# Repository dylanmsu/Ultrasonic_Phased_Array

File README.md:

# Ultrasonic_Phased_Array
This repository is under construction and will contain all the sources for a working ultrasonic phased array.
The vitis project in this repository is to be used in a accoustic levitation example.

## Working principle
Lets consider an example where we want to send a single pulse of airpressure to a certain point in space. We have an array of transducers we can work with. Since the waves travel in a sphere around the transducers, we can time the pulses at each transducer in such a way that all the wavefronts arrive at the same time in a single focal point. This is illustrated in the animation below.

If we were to send a sinewave with the same delay through the transducers instead of a single pulse, all the peaks and troughs of those waves would ideally only add up in the focal point. The amplitude would then be the greatest at that point and ideally cancel out everywhere else. This is actually not always the case because a side effect of using a periodic signal is that we create te posibility of sidelobes. Sidelobes are areas where some of the sinewaves constructively add up unwantedly where the phase shift is a multiple of 360 degrees. To prevent the occurance of sidelobes, we need to space the transducers with a distance between 1/2 wavelength, and 1/4 wavelength. 

To calculate the phase offsets per transducer for a single focal point, the following formula is used:
$$\varphi =  -\frac{2\pi\sqrt{(X_t - X_f)^2 + (Y_t - Y_f)^2 + (Z_t - Z_f)^2}}{\lambda}$$
Where: 
- $\varphi$ = the phase offset for a given transducer
- $X_t, Y_t, Z_t$ = the location of the transducer
- $X_f, Y_f, Z_f$ = the location of the focal point
- $\lambda$ = wavelength

The waves exiting the transducers will look something like this.

The red dots at the bottom are sources emitting pure sinusodial signals with an adjusted phase delay so all the waves are in phase at the red dot around the middle.

There is an included python script called 'wave_equation.py' that focuses the waves to your mouse location by manipulating the phases of the emitters. It solves the 2d wave equation so it should be more acurate than the above animation.

We can also steer a beam into a specified direction. To do this we have to align the wavefronts into a plane where its normal vector points to the direction of travel. This is illustrated in 2d in the animation below. 

Here the phase offsets are calculated using the following formula:
$$\varphi = \frac{2\pi(aX_t+bY_t-Z_t)}{\lambda\sqrt{1+a^2+b^2}}$$
Where: 
- $\varphi$ = the phase offset for a given transducer
- $X_t, Y_t, Z_t$ = the location of the transducer
- $a$ = the slope of the tangent plane in the x-axis
- $b$ = the slope of the tangent plane in the y-axis
- $\lambda$ = wavelength

The waves exiting the transducers will look something like this.

In the case for this project, the spacing between the sources is 10 mm wich is more than double the recommended wavelength so we expect some loss of energy through sidelobes. Even more so diagonally since the sources are placed in a rectangular grid and the diagonal spacing is 14.14 mm. Placing the sources in a hexagonal grid solves big diagonal spacing but this makes the design of the PCB more challanging. For this reason i opted to design a rectangular grid of sources anyway.

## Setup
There are two array's used in the levitation example. One is facing upwards and the other is facing downwards. They are facing eachother with a distance of 70mm. This distance is arbitrarily chosen based on the needed volume for levitation.

## FPGA
The FPGA used in this project is the ZYNQ XC7Z020 on a Zybo Z7 board but any Zynq FPGA should work. The FPGA contains two distinct parts: The processing system (PS) and the programmable logic (PL):

### Programmable Logic
The PL contains an implementation which receives 7 bit values from the PS (Processing System) for every transducer. This value sets the phase of the output signal. This is acheived by making a fifo of length = 2^7 in the case of a phase resolution of 7 bits. The 40KHz signal is fed into the fifo at 40KHz * 2^7 = 5.12MHz. The reason for this is because we want exactly 1 full period of the signal in the fifo. The 7 bit value determines at which address of the fifo the output signal is tapped from. This way wan can adjust the phase of the output signal in 2^7 steps per period.

The block diagram that takes an AXI peripheral bus and outputs a serial data stream to drive the included transducer board is illustrated below. 

here is an overview of the in- and output signals:
- **signal_in**: this is the signal that will drive the transducers and whos phase will be altered, in our case this signal would have a 50% dutycycle at 40KHz.
- **fifo_clk**: this is the clock that shifts the fifo's used for the delay generation. This should be 2^7 times faster than the 40KHz signal. in this case the fifo length and so the phase resolution is 2^7. This means a frequency of 5.12MHz.
- **ser_clk**: this is the serial clock that drives the serializer and also the shift registers on the transducer board. This clock should be 5x the 'fifo_clock' if each shift register drives 5 transducers. This means a frequency of 25.6MHz.
- **s00_axi_aclk**: this is the AXI peripheral clock comming directly from the Processing system.
- **en**: enable the output signal.
- **resetn**: active low reset signal.
- **S00_AXI**: AXI slave port
- **pmod_out**: this port goes directly to a Pmod port on the FPGA-board and drives the transducer board.

The AXI peripheral IP_block generates the delayed signals and outputs them as a 25 bit vector. This vector is split into 5x 5 bit vectors by the xlslice blocks. The 5 bit vectors enter the seializer. The data is then clocked bit by bit to the output.

### Implementation

TODO

### Processing System
The Processing system sends data to the FPGA facric which adjusts the phase offsets of the physical transducers.

### Practical limitations
In an ideal world the signal applied to the physical transducer should give the same signal in air pressure. That is however not the case. For every transducer there is a significant random phase shift present. This will completely negate our effort to acheive a phased array. So we have to measure the phase shift of every transducer and incorporate this into the phase calculations.

### Video
Below is a video showing two ultrasonic arrays levitating a piece of styrofoam in an preprogrammed path.

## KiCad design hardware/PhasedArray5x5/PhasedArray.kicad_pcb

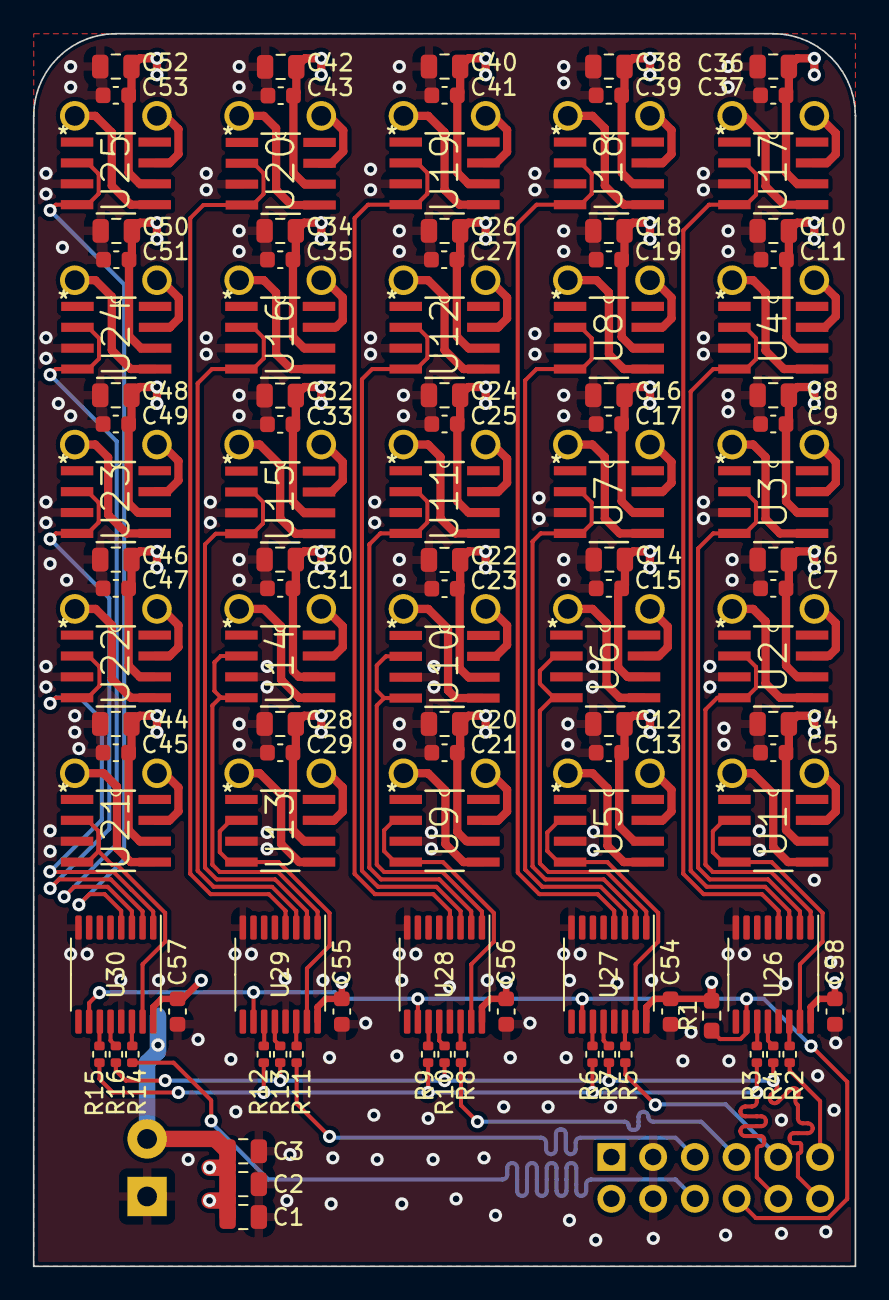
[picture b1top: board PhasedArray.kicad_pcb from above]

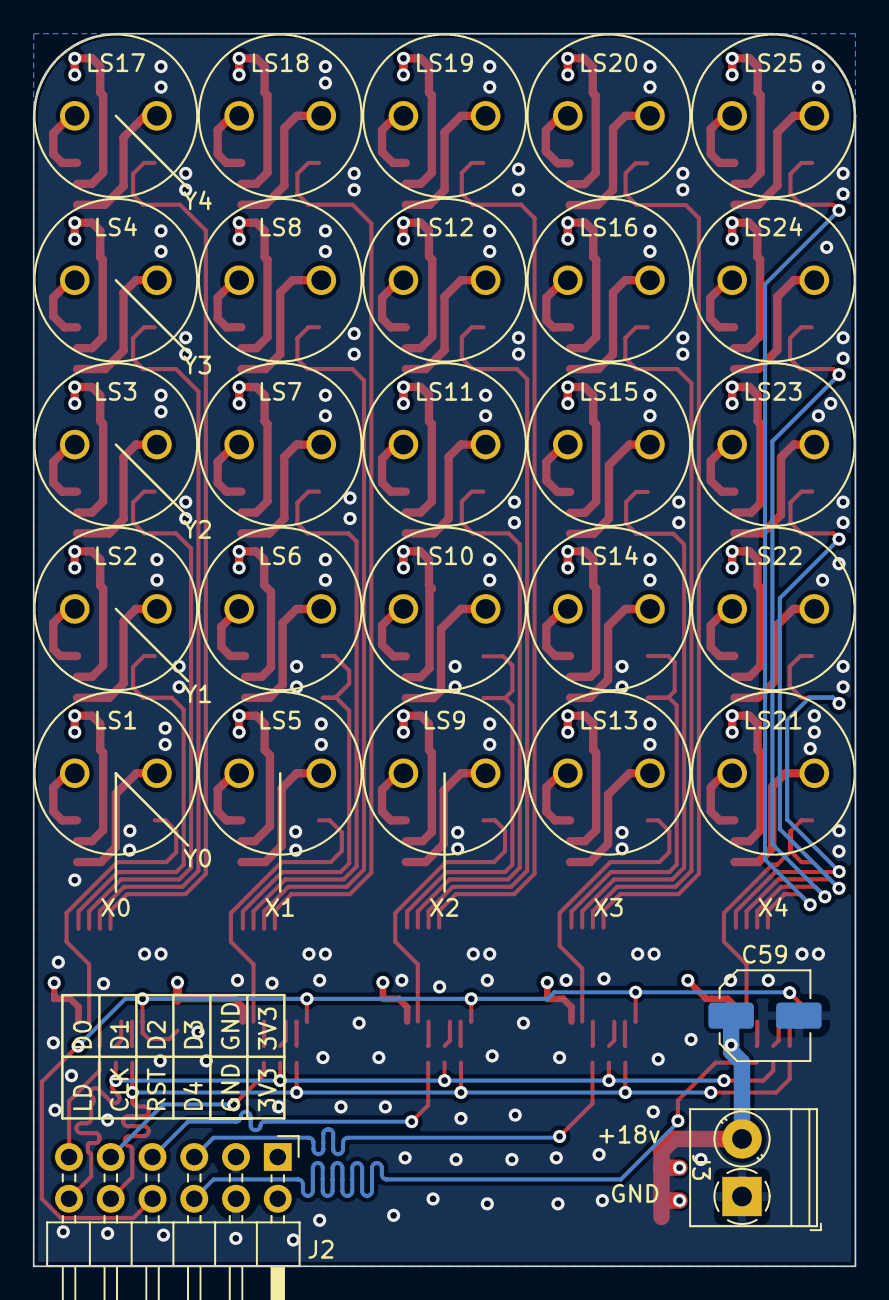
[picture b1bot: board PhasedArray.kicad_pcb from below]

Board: 4 copper layers, 50.0 x 75.0 mm, 132 parts (28 on the bottom side), 101 nets.

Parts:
C1, C2, C3, C4, C6, C8, C10, C12, C14, C16, C18, C20, C22, C24, C26, C28, C30, C32, C34, C36, C38, C40, C42, C44, C46, C48, C50, C52: 4.7uF; C_0805_2012Metric
C5, C7, C9, C11, C13, C15, C17, C19, C21, C23, C25, C27, C29, C31, C33, C35, C37, C39, C41, C43, C45, C47, C49, C51, C53, C54, C55, C56, C57, C58: 100nF; C_0603_1608Metric
C59: 47uF; C_Elec_5x5.4
J2: Conn_02x06_Odd_Even; PinHeader_2x06_P2.54mm_Horizontal
J3: Screw_Terminal_01x02; TerminalBlock_Phoenix_PT-1,5-2-3.5-H_1x02_P3.50mm_Horizontal
LS1, LS2, LS3, LS4, LS5, LS6, LS7, LS8, LS9, LS10, LS11, LS12, LS13, LS14, LS15, LS16, LS17, LS18, LS19, LS20, LS21, LS22, LS23, LS24, LS25: Speaker_Ultrasound; XDCR_MA40S4R
R1: 0R; R_0603_1608Metric_Pad0.98x0.95mm_HandSolder
R2, R3, R4, R5, R6, R7, R8, R9, R10, R11, R12, R13, R14, R15, R16: 39R; R_0402_1005Metric
U1, U2, U3, U4, U5, U6, U7, U8, U9, U10, U11, U12, U13, U14, U15, U16, U17, U18, U19, U20, U21, U22, U23, U24, U25: TC4428AEOA; SOIC127P600X175-8N
U26, U27, U28, U29, U30: 74AHCT595; TSSOP-16_4.4x5mm_P0.65mm

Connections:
+3V3: C54.1, C55.1, C56.1, C57.1, C58.1, J2.1, J2.2, R1.2, U26.16 (VCC), U27.16 (VCC), U28.16 (VCC), U29.16 (VCC), U30.16 (VCC)
+15V: C1.1, C2.1, C3.1, C4.1, C5.1, C6.1, C7.1, C8.1, C9.1, C10.1, C11.1, C12.1, C13.1, C14.1, C15.1, C16.1, C17.1, C18.1, C19.1, C20.1, C21.1, C22.1, C23.1, C24.1, C25.1, C26.1, C27.1, C28.1, C29.1, C30.1, C31.1, C32.1, C33.1, C34.1, C35.1, C36.1, C37.1, C38.1, C39.1, C40.1, C41.1, C42.1, C43.1, C44.1, C45.1, C46.1, C47.1, C48.1, C49.1, C50.1, C51.1, C52.1, C53.1, C59.1, J3.2, U1.6 (VDD), U2.6 (VDD), U3.6 (VDD), U4.6 (VDD), U5.6 (VDD), U6.6 (VDD), U7.6 (VDD), U8.6 (VDD), U9.6 (VDD), U10.6 (VDD), U11.6 (VDD), U12.6 (VDD), U13.6 (VDD), U14.6 (VDD), U15.6 (VDD), U16.6 (VDD), U17.6 (VDD), U18.6 (VDD), U19.6 (VDD), U20.6 (VDD), U21.6 (VDD), U22.6 (VDD), U23.6 (VDD), U24.6 (VDD), U25.6 (VDD)
CLK: J2.10, R3.1, R6.1, R9.1, R12.1, R15.1
GND: C1.2, C2.2, C3.2, C4.2, C5.2, C6.2, C7.2, C8.2, C9.2, C10.2, C11.2, C12.2, C13.2, C14.2, C15.2, C16.2, C17.2, C18.2, C19.2, C20.2, C21.2, C22.2, C23.2, C24.2, C25.2, C26.2, C27.2, C28.2, C29.2, C30.2, C31.2, C32.2, C33.2, C34.2, C35.2, C36.2, C37.2, C38.2, C39.2, C40.2, C41.2, C42.2, C43.2, C44.2, C45.2, C46.2, C47.2, C48.2, C49.2, C50.2, C51.2, C52.2, C53.2, C54.2, C55.2, C56.2, C57.2, C58.2, C59.2, J2.3, J2.4, J3.1, U1.3 (GND), U2.3 (GND), U3.3 (GND), U4.3 (GND), U5.3 (GND), U6.3 (GND), U7.3 (GND), U8.3 (GND), U9.3 (GND), U10.3 (GND), U11.3 (GND), U12.3 (GND), U13.3 (GND), U14.3 (GND), U15.3 (GND), U16.3 (GND), U17.3 (GND), U18.3 (GND), U19.3 (GND), U20.3 (GND), U21.3 (GND), U22.3 (GND), U23.3 (GND), U24.3 (GND), U25.3 (GND), U26.8 (GND), U26.13 (~OE), U27.8 (GND), U27.13 (~OE), U28.8 (GND), U28.13 (~OE), U29.8 (GND), U29.13 (~OE), U30.8 (GND), U30.13 (~OE)
LOAD: J2.12, R4.1, R7.1, R10.1, R13.1, R16.1
unnamed: LS1.1, U1.7 (*OUT_A)
unnamed: LS1.2, U1.5 (*OUT_B)
unnamed: LS2.1, U2.7 (*OUT_A)
unnamed: LS2.2, U2.5 (*OUT_B)
unnamed: LS3.1, U3.7 (*OUT_A)
unnamed: LS3.2, U3.5 (*OUT_B)
unnamed: LS4.1, U4.7 (*OUT_A)
unnamed: LS4.2, U4.5 (*OUT_B)
unnamed: LS5.1, U5.7 (*OUT_A)
unnamed: LS5.2, U5.5 (*OUT_B)
unnamed: LS6.1, U6.7 (*OUT_A)
unnamed: LS6.2, U6.5 (*OUT_B)
unnamed: LS7.1, U7.7 (*OUT_A)
unnamed: LS7.2, U7.5 (*OUT_B)
unnamed: LS8.1, U8.7 (*OUT_A)
unnamed: LS8.2, U8.5 (*OUT_B)
unnamed: LS9.1, U9.7 (*OUT_A)
unnamed: LS9.2, U9.5 (*OUT_B)
unnamed: LS10.1, U10.7 (*OUT_A)
unnamed: LS10.2, U10.5 (*OUT_B)
unnamed: LS11.1, U11.7 (*OUT_A)
unnamed: LS11.2, U11.5 (*OUT_B)
unnamed: LS12.1, U12.7 (*OUT_A)
unnamed: LS12.2, U12.5 (*OUT_B)
unnamed: LS13.1, U13.7 (*OUT_A)
unnamed: LS13.2, U13.5 (*OUT_B)
unnamed: LS14.1, U14.7 (*OUT_A)
unnamed: LS14.2, U14.5 (*OUT_B)
unnamed: LS15.1, U15.7 (*OUT_A)
unnamed: LS15.2, U15.5 (*OUT_B)
unnamed: LS16.1, U16.7 (*OUT_A)
unnamed: LS16.2, U16.5 (*OUT_B)
unnamed: LS17.1, U17.7 (*OUT_A)
unnamed: LS17.2, U17.5 (*OUT_B)
unnamed: LS18.1, U18.7 (*OUT_A)
unnamed: LS18.2, U18.5 (*OUT_B)
unnamed: LS19.1, U19.7 (*OUT_A)
unnamed: LS19.2, U19.5 (*OUT_B)
unnamed: LS20.1, U20.7 (*OUT_A)
unnamed: LS20.2, U20.5 (*OUT_B)
unnamed: LS21.1, U21.7 (*OUT_A)
unnamed: LS21.2, U21.5 (*OUT_B)
unnamed: LS22.1, U22.7 (*OUT_A)
unnamed: LS22.2, U22.5 (*OUT_B)
unnamed: LS23.1, U23.7 (*OUT_A)
unnamed: LS23.2, U23.5 (*OUT_B)
unnamed: LS24.1, U24.7 (*OUT_A)
unnamed: LS24.2, U24.5 (*OUT_B)
unnamed: LS25.1, U25.7 (*OUT_A)
unnamed: LS25.2, U25.5 (*OUT_B)
unnamed: R3.2, U26.11 (SRCLK)
unnamed: R4.2, U26.12 (RCLK)
unnamed: R2.2, U26.14 (SER)
unnamed: R6.2, U27.11 (SRCLK)
unnamed: R7.2, U27.12 (RCLK)
unnamed: R5.2, U27.14 (SER)
unnamed: R9.2, U28.11 (SRCLK)
unnamed: R10.2, U28.12 (RCLK)
unnamed: R8.2, U28.14 (SER)
unnamed: R12.2, U29.11 (SRCLK)
unnamed: R13.2, U29.12 (RCLK)
unnamed: R11.2, U29.14 (SER)
unnamed: R15.2, U30.11 (SRCLK)
unnamed: R16.2, U30.12 (RCLK)
unnamed: R14.2, U30.14 (SER)
RESET: J2.8, R1.1, U26.10 (~SRCLR), U27.10 (~SRCLR), U28.10 (~SRCLR), U29.10 (~SRCLR), U30.10 (~SRCLR)
SER0: J2.11, R2.1
SER1: J2.9, R5.1
SER2: J2.7, R8.1
SER3: J2.5, R11.1
SER4: J2.6, R14.1
input00: U1.2 (IN_A), U1.4 (IN_B), U26.15 (QA)
input01: U2.2 (IN_A), U2.4 (IN_B), U26.1 (QB)
input02: U3.2 (IN_A), U3.4 (IN_B), U26.2 (QC)
input03: U4.2 (IN_A), U4.4 (IN_B), U26.3 (QD)
input04: U17.2 (IN_A), U17.4 (IN_B), U26.4 (QE)
input10: U5.2 (IN_A), U5.4 (IN_B), U27.15 (QA)
input11: U6.2 (IN_A), U6.4 (IN_B), U27.1 (QB)
input12: U7.2 (IN_A), U7.4 (IN_B), U27.2 (QC)
input13: U8.2 (IN_A), U8.4 (IN_B), U27.3 (QD)
input14: U18.2 (IN_A), U18.4 (IN_B), U27.4 (QE)
input20: U9.2 (IN_A), U9.4 (IN_B), U28.15 (QA)
input21: U10.2 (IN_A), U10.4 (IN_B), U28.1 (QB)
input22: U11.2 (IN_A), U11.4 (IN_B), U28.2 (QC)
input23: U12.2 (IN_A), U12.4 (IN_B), U28.3 (QD)
input24: U19.2 (IN_A), U19.4 (IN_B), U28.4 (QE)
input30: U13.2 (IN_A), U13.4 (IN_B), U29.15 (QA)
input31: U14.2 (IN_A), U14.4 (IN_B), U29.1 (QB)
input32: U15.2 (IN_A), U15.4 (IN_B), U29.2 (QC)
input33: U16.2 (IN_A), U16.4 (IN_B), U29.3 (QD)
input34: U20.2 (IN_A), U20.4 (IN_B), U29.4 (QE)
input40: U21.2 (IN_A), U21.4 (IN_B), U30.15 (QA)
input41: U22.2 (IN_A), U22.4 (IN_B), U30.1 (QB)
input42: U23.2 (IN_A), U23.4 (IN_B), U30.2 (QC)
input43: U24.2 (IN_A), U24.4 (IN_B), U30.3 (QD)
input44: U25.2 (IN_A), U25.4 (IN_B), U30.4 (QE)

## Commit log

2022-10-11 added documentation
2022-10-12 added image
2022-11-09 added python simulation script
2023-03-20 Create LICENCE
2023-03-20 Update LICENCE
2023-04-05 add vivado sources
2023-05-01 added beam forming animation
